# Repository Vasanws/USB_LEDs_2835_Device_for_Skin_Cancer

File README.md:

# USB LED Device for Skin Cancer  
In this project will show how to made Printed Circuit Board (PCB) for USB LED for Skin Cancer done from software design to transferring onto copper board as a prototype.

# How does USB LED for Skin Cancer works?  
The LEDs light wavelength was chosen specifically by the power of the light intensity it emits. A special cream applys on the affected area of the human skin and once the speical cream expose by the LEDs light, the special cream enter the skin and destroys the cancer cells.  

# How to do it as Prototype?  
There are many methods out there on creating PCB, for the best result is by using heat method with high temperature around 220 degree celcius. The tools can be use are iron or laminated machine (heavy duty). For this project, using laminated machine is one of the best tool to produce consistency in tranferring the circuit onto a copper board.  

# Step 1: Tools and Materials requires
Tools 
- Laminated Machine (heavy duty).
- Cutting mat.
- Cutting knife.
- Overhead projector or torchlight.
- Laser printer.
- Milling machine (drill)
- Gloves.
- Eye protection.
- Etching tray.
- Container for water.
- Container or beaker for PCB tinning.
- Hotplate.
- Kicad 6.
- Inkscape.
- Multimeter.
- Sanding machine.

Materials
- Semi-gloss paper 230gsm or lower gms.
- Etching Solution (Ferric Chloride).
- Thiourea (12.5 grams).
- Tartaric acid (8.8 grams).
- Tin(II) Chloride (1.3 grams). 
- tap water (250ml).
- Acetone.
- Sandpaper.
- Tipped marker pen.
- Aluminium foil.
- Copper board.
- Sponge.
- Soap

# Step 2: Making circuit board design 
In Kicad 6 software is where to design the circuit layout as shown below.

# Step 3: Toner Tranfer 
In this step will show the method how to toner transfer the circuit layout from the software onto a physical board. Firstly, printout the circuit layout onto semi gloss paper. For better result, ensure that the ink are darker black after printout and stick on the semi gloss paper and no extras ink act of debris that interfere the layout's connections. If the printout is not good, clean the roller in the printer to remove ink debris or check if enough ink. To printout duplicate circuit layout in a single paper, use Inkscape to duplicate the circuit layout as shown below:

Before proceed to to transfer the circuit layout on the board, the copper board surface requires to be clean from oxidation and surface debris. To do that, use sandpaper and sand the copper board surface until the surface turns into a shining copper colour. Once it is done, rinse the copper board with tap water apply soap and scrub with a sponge to ensure left no dirt on the copper board surface. Finally, apply acetone on the copper board surface and wipe with cloth or tissue. The picture below shows before and after of the copper board surface. 

Before:

After: 

Then, place the printed circuit layout on the surface of the copper board. Make sure that the printed circuit layout ink directly touch the copper board surface as shown below.

Before:

After:

Place the aluminium foil on the surface where the printout cricuit layout gloss paper is. After few try and error, this way allows the heat transfer across the board evenly for aa large scale printout circuit layout and also for smaller singular printout circuit layout.

Then, place the board either front or back of the laminated machine depending on the model features and feed it into the laminated machine with the maximum temperature around 200 degree celcius to 220 degree celcius repeatedly. Lowest count is 35 counts of feed. This is because the laminated machine is moving at a moderate rolling speed so it require to feed it multiple counts. To make it a single count, the motor of the laminated machine requires to be modify to the slowest rolling speed. Ensure that wear gloves to avoid skin burn during the handling.

Set laminated machine temperature to maximum as shown below:

Here is an example of a trial without the aluminium foil. In this example uses a smaller scale of a singular board as the method shares the same. 

After multiple counts the copper board being feed into the laminated machine, move the copper board away from the laminated machine and cool the copper board. After the copper board is cool off, place the copper board into a container of tap water and let the gloss paper become soft and soggy and safely to peal off for about 10 minutes to 15 minutes. To indicate when will the gloss paper to be peal off, look at the contrast of the circuit layout once it become clear to see through and the gloss paper is soggy that indicates the gloss paper can be peal off and the ink will not be remove from the copper board.

Before:

After:

Once the circuit layout can be seen under the water, peal the paper off the from the board.

As the picture above, the toner transfer is not perfect nor close to perfect as some of the tracers or component footprint did not stick on the copper board. This shows that the heat transfer across the board does not reach the same level of heat during the laminating process.

Now with the aluminium foil cover the copper board and repeat the same process here is the result. Do some inspection after the pealing the gloss paper, if there is excessive paper stuck in between the circuit layout or blocking the drilling holes, use wet cloth and gentle scrap off the excessive paper that stuck on the copper board. This will later during the etching process will be easy to etch. Tested where if the excessive paper does not remove, the board will not etch properly and may excessive etching will remove the ink.

Laslty, use a tipped marker pen or permanent marker pen to do some touch up if some of the ink does not stick on the copper board. For example highlighting tracks or empty space or component footprints.

In conclusion for Step 3, to reduce extra work from redo if the toner transfer fail, do the following:
- Clean the copper board surface with sandpaper and wash with soap and scrub with sponge.
- Cover the copper board with aluminium foil once the printed circuit layout is place on the copper board.
- During the laminating process, ensure that the copper board go through at least 40 counts consistently.
- Once done, cool the copper board and place the copper board into a container of tap water to soften the gloss paper.
- Once the printed circuit layout can be see through from the gloss paper, slowly peal the gloss paper.
- Clear away any excessive paper on the board.
- Double check if there is any missing ink on the circuit layout and touch up with a tipped marker pen.

# Step 4: Etching
Before etching, recommend to cut the copper board which contains the circuit layout only to reduce waste of copper board and easier for etching for each circuit layout. Use PCB Cutter or PCB Shear or ready cut the size of the copper board of the desire size before implementing Step 3 Toner Transfer.

Steps to do etching:
- Place the copper board into an etching tray.
- Pour an amount Ferric Chloride into the etching tray.
- Tilt the etching tray left and right or vice versa to let the acid reaction active.
- Do this for about 10 to 15 minutes or lesser depending on how strong the acid reaction is.
- Check the copper board time to time whether it is completely etch off the expose copper.
- Use glove or plactic clamp to remove the board once it is done and leaving it for too long may remove the ink protected area.
- Wash the board with tap water to remove the remaining acid on the board's surface.

Once the etching is done, use acetone with cloth or tissue to remove the ink.

Use multimeter to check each connectivity whether there any copper being etch away. This is to ensure that the board does not have any defects or fixable and reuseable before solder the components on the board. May use lights to place under the board to check the overall copper trace. For example, the board is being place under a overhead projector:

This way gives a clear view to troubleshoot the copper trace. This method only works for single-sided layout.

# Step 5: Drilling the Holes
For this step, may use a Milling Drill machine or Hand Drill. In this project for the drilling uses Milling Drill machine for better drilling accuracy by hand. Drill all the board's holes.

# Step 6: Board Shaping
In this step is more towards on shaping the board following the circuit layout design. In this project the shaping done by using a sanding machine.

Before:

After:

# Step 7: PCB Tinning
Why is PCB tinning is needed? PCB tinning protects the expose copper from being oxidation and corrosion. Tinning will prolong the copper tracers to remain in good shape and functionality in its conductivity. Without tinning, the oxidation in the copper can results in difficulties in soldering.

How to create DIY tinning?
- Get a beaker or plastic container.
- Fill in 250ml of tap water.
- Heat the water using hotplate 100 degree celcius.
- Mix the chemical as following: Thiourea = 12.5 grams, Tartaric acid = 8.8 grams, Tin(II) Chloride = 1.3 grams.
- Stir the following chemicals while heating up on the hotplate.
- To know whether the chemical is ready, visual change can be seen when the liquid turns cloudy and if the liquid surface have bubbles, remove from the hotplate.
- Dip the board into the liquid and once the copper is tinned, do the next side of the board.

Comparison between tinning copper trace and non tinning copper trace.

Finishing of tinning copper trace.

---------------------------------------------------------------------------------------------------------------------
# CHANGELOG OF THE PROTOTYPE TO FINAL CIRCUIT LAYOUT
This is a layout of a USB LEDs with SMD LED component imperial code 2835. 
This is the showcase of the finished layout.  
PCB layout version 1    

Size of the layout  
Length - 100mm  
Width - 20mm

PCB layout update version 2  
 
Changelog: 
1. Added from 28 LEDs to 32 LEDs. 
2. Reposition all LEDs from diagonal positions to horizontal positions.  
3. Moves the components more outwards nearby the edge cut to make room for the LEDs spacing.  
4. Reposition U3 to the right side of the layout. 
5. Reposition other components from diagonal positions to vertical and horizontal positions.  
6. Reduce the radius Front Courtyard for both mounting hole to 0.4mm radius.  
7. The copper filler for the LED connections are set to, Pad connections: Thermal reliefs, Thermal relief gap: 0.2mm, Thermal spoke width: 0.8mm. 
8. All resistor and capacitor have been changed from 0603 to 0402 except Rx1 from 0603 to 1206. 

PCB layout update version 3  

Changelog:  
1. Added two jumper in the layout for touch sensor. 
2. Expend the copper fill between the LEDS. 

PCB layout update version 4  

Changelog:  
1. Edit LED footprint distance between two pads = 0.61mm. 
2. Route crisscross tracer between LEDs to LED's driver.  
3. Additional tracer for 5V pass through between the LED footprint with tracer size 0.2mm.  
4. Replace R1 footprint from 0402 to 0603.  
  
Schematic diagram layout 1      

Circuit layout update   
     
Changelog:
1. Added copper fill zone to unconnected footprint of the inverter logic U3 (pin 1). Copper fill zone with settings zone priority level : 1, clearance : 0.2mm, Pad connections : Thermal reliefs, Thermal relief gap : 0.2mm
2. Changed the size of CX1 footprint to 0603 and value to 22uF in schematic diagram.
    
PCB layout update version 5    
   
Changelog:    
1. Custom made footprint SOD-323 for D33 based on the measurement of this model https://www.vishay.com/docs/85751/1n4148ws.pdf    
2. Rearrange the components to be closer and allow some spaces for larger components.   
3. Added copper fill 5V to fill in the empty spaces on the left side of the board.    
4. Retrace the track of the connection for cleaner connection.    
    
Schematic diagran layout 2    

Changelog:    
1. Added TVS diode conneted to C2.    
    
PCB layout update version 6   

Changelog:    
1. Image 1 modified the testpoint hole with overlapping square pad for soldering.   
2. Image 2 modified L1 according to the specification WHC 0630 https://offer-product.oss-cn-beijing.aliyuncs.com/product/offer/attachment/2140865164/file/subPdf_4274_10144_20210414-212909770.pdf with some adjustment length : 7.7mm, pads size y-axis : 3.5mm.    
3. Remove front solder mask at the right side of the board with together with the L1 to expand soldering of larger or smaller inductor component and expose empty area for power wires.   

PCB layout update version 7   
Changelog:    
1. Update mounting hole size from 2mm to 2.2mm.
2. Slightly move D35 closer to right side mounting hole with distance between each other 0.3mm.   
3. Fix Electrical Rules Error in schemactic symbols by creating and saving custom symbols in project.   

PCB layout update version 8   

Changelog:    
1. Cleanup copper fill to make the workspace clean.   
2. Custom resistor footprint for Rx1 combine metrics (1206/0805).

PCB layout update verion 9  
Changelog:  
1. Change R6 resistor value to 990 ohm.
2. Change C5 capacitor value to 33nF.

PCB Paneling  
PCB paneling for fabrication.  

Final fabrication  

-------------------------------------------------------------------------------------------------------------   
How to install Kikit in Kicad6 ?    
1. Open Kicad 6.0   
2. At the menu of Kicad 6.0, search **"Plugin and Content Manager"** under **tools** or can be seen from the right of the menu or **Ctrl + M**.   
3. Select **Plugins** Tab and search for **KiKit** and click install. Select **Libraies** tab and search for **KiKit Library** and click install.   
4. Click Apply Changes to proceed installation.   
5. Open pcbnew and under **Tools** search **External Plugins** and click refresh plugins.   
6. If plugins didn't shown, open **Kicad 6 Command Prompt**.    
7. In Command Prompt, enter **pip install kikit**.    
8. Once done, open pcbnew and refresh plugins.    
Installation guide can be found here: https://pypi.org/project/KiKit/

-------------------------------------------------------------------------------------------------------------
# REFERENCES
- Home-made mixture for chemical PCB tinning (acid bath) - https://robertgawron.blogspot.com/2016/04/galvanic-pcb-tinning-by-using-home-made.html
- Make Homemade PCB Tinning solution ("Liquid Tin") - https://www.reddit.com/r/electronics/comments/77tcpb/make_homemade_pcb_tinning_solution_liquid_tin/
- How to Make Double Sided Circuit Boards at Home - https://www.youtube.com/watch?v=au2ba5gWLWk

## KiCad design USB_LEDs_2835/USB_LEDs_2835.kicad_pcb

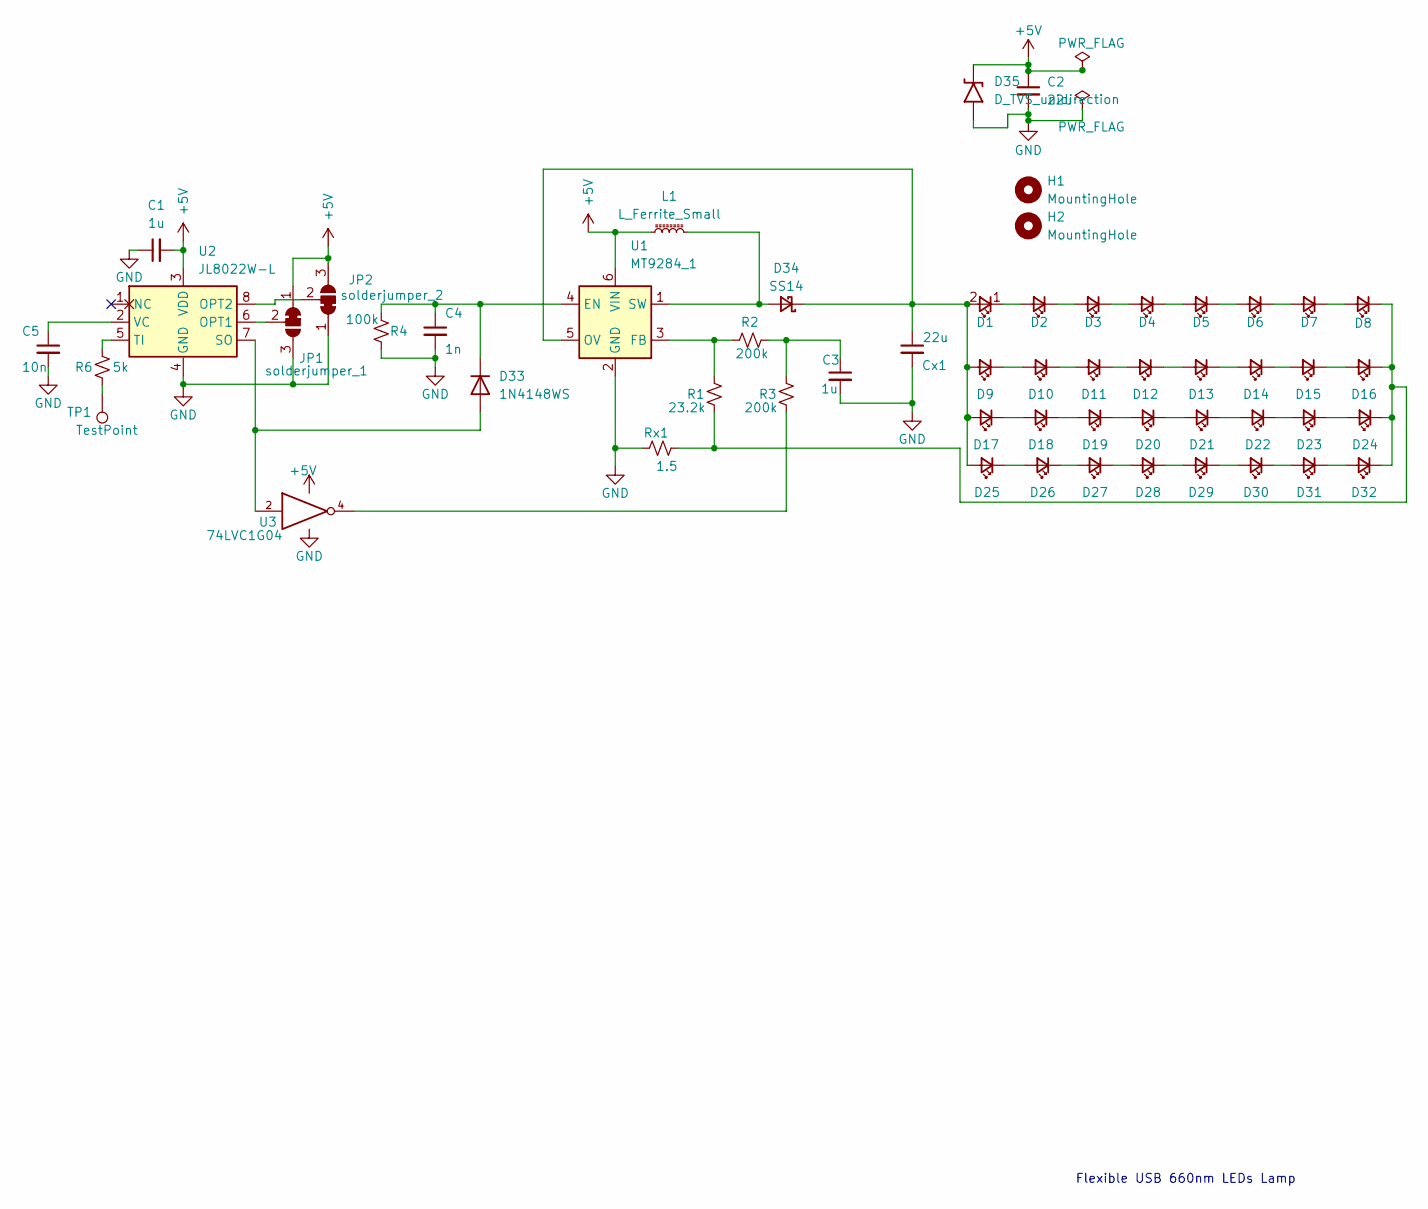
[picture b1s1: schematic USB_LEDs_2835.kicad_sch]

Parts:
C1, C3: 1u; C_0402_1005Metric
C2: 22u; C_0603_1608Metric
C4: 1n; C_0402_1005Metric
C5: 10n; C_0402_1005Metric
Cx1: 22u; C_0603_1608Metric
D1, D2, D3, D4, D5, D6, D7, D8, D9, D10, D11, D12, D13, D14, D15, D16, D17, D18, D19, D20, D21, D22, D23, D24, D25, D26, D27, D28, D29, D30, D31, D32: 660nm; LED_2835_custom_margin
D33: 1N4148WS; D_SOD-323_custom
D34: SS14; D_SMA
D35: D_TVS_unidirection; D_SOD-923
H1, H2: MountingHole; MountingHole_2.1mm
JP1: solderjumper_1; SolderJumper-3_P1.3mm_Bridged12_Pad1.0x1.5mm_NumberLabels
JP2: solderjumper_2; SolderJumper-3_P1.3mm_Bridged12_Pad1.0x1.5mm_NumberLabels
L1: L_Ferrite_Small; L_WHC_0630_custom
R1: 23.2k; R_0603_1608Metric
R2, R3: 200k; R_0402_1005Metric
R4: 100k; R_0402_1005Metric
R6: 5k; R_0402_1005Metric
Rx1: 1.5; R_1206_0805_3216Metric_custom
TP1: TestPoint; TestPoint_Loop_D2.50mm_Drill1.0mm_overlap_pad_custom
U1: MT9284_1; SOT-23-6
U2: JL8022W-L; SOIC-8_3.9x4.9mm_P1.27mm
U3: 74LVC1G04; SOT-353_SC-70-5

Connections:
+5V: C1.2, C2.1, D35.1 (A1), JP1.1 (A), JP2.3 (B), L1.1, U1.6 (VIN), U2.3 (VDD), U3.5 (VCC)
GND: C1.1, C2.2, C3.2, C4.2, C5.2, Cx1.2, D35.2 (A2), JP1.3 (B), JP2.1 (A), R4.1, Rx1.1, U1.2 (GND), U2.4 (GND), U3.3 (GND)
unnamed: C3.1, R2.2, R3.2
unnamed: C4.1, D33.1 (K), R4.2, U1.4 (EN)
unnamed: C5.1, U2.2 (VC)
unnamed: Cx1.1, D1.2 (A), D9.2 (A), D17.2 (A), D25.2 (A), D34.1 (K), U1.5 (OV)
unnamed: D1.1 (K), D2.2 (A)
unnamed: D2.1 (K), D3.2 (A)
unnamed: D3.1 (K), D4.2 (A)
unnamed: D4.1 (K), D5.2 (A)
unnamed: D5.1 (K), D6.2 (A)
unnamed: D6.1 (K), D7.2 (A)
unnamed: D7.1 (K), D8.2 (A)
unnamed: D10.1 (K), D11.2 (A)
unnamed: D9.1 (K), D10.2 (A)
unnamed: D11.1 (K), D12.2 (A)
unnamed: D12.1 (K), D13.2 (A)
unnamed: D13.1 (K), D14.2 (A)
unnamed: D14.1 (K), D15.2 (A)
unnamed: D15.1 (K), D16.2 (A)
unnamed: D8.1 (K), D16.1 (K), D24.1 (K), D32.1 (K), R1.1, Rx1.2
unnamed: D17.1 (K), D18.2 (A)
unnamed: D18.1 (K), D19.2 (A)
unnamed: D19.1 (K), D20.2 (A)
unnamed: D20.1 (K), D21.2 (A)
unnamed: D21.1 (K), D22.2 (A)
unnamed: D22.1 (K), D23.2 (A)
unnamed: D23.1 (K), D24.2 (A)
unnamed: D25.1 (K), D26.2 (A)
unnamed: D26.1 (K), D27.2 (A)
unnamed: D27.1 (K), D28.2 (A)
unnamed: D28.1 (K), D29.2 (A)
unnamed: D29.1 (K), D30.2 (A)
unnamed: D30.1 (K), D31.2 (A)
unnamed: D31.1 (K), D32.2 (A)
unnamed: D33.2 (A), U2.7 (SO), U3.2
unnamed: D34.2 (A), L1.2, U1.1 (SW)
unnamed: JP1.2 (C), U2.6 (OPT1)
unnamed: JP2.2 (C), U2.8 (OPT2)
unnamed: R1.2, R2.1, U1.3 (FB)
unnamed: R3.1, U3.4
unnamed: R6.1, TP1.1
unnamed: R6.2, U2.5 (TI)

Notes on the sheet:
Flexible USB 660nm LEDs Lamp

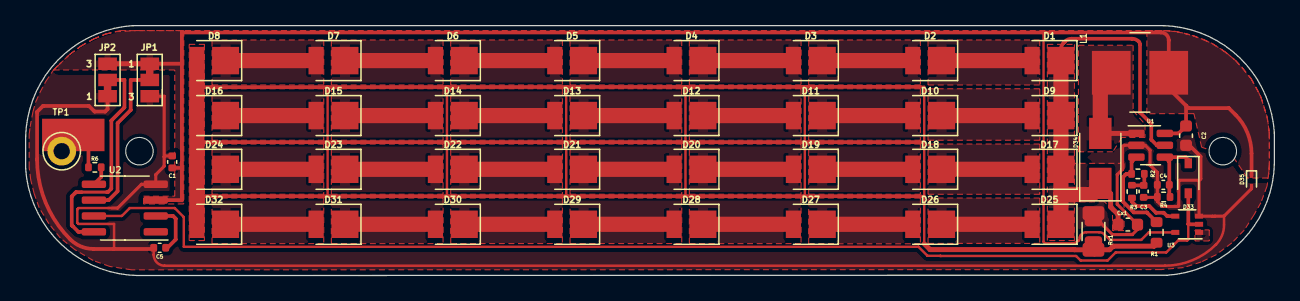
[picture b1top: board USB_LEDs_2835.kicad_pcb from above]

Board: 2 copper layers, 99.9 x 20.0 mm, 56 parts (0 on the bottom side), 43 nets.

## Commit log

2023-05-11 Relocated components and compacting the area used
